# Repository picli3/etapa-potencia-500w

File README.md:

# etapa-potencia-500w

Barra de potencia de audio con múltiples transistores en paralelo, pensada para entregar alta corriente y robustez térmica en amplificadores de gran potencia.

## Qué incluye
- esquemáticos o archivos de diseño en KiCad
- PCB o documentación asociada
- base reutilizable para análisis, fabricación o mejora del proyecto

## Propósito general
Este repositorio busca concentrar el diseño de hardware del proyecto en un formato editable y reutilizable, facilitando pruebas, documentación y futuras iteraciones del circuito.

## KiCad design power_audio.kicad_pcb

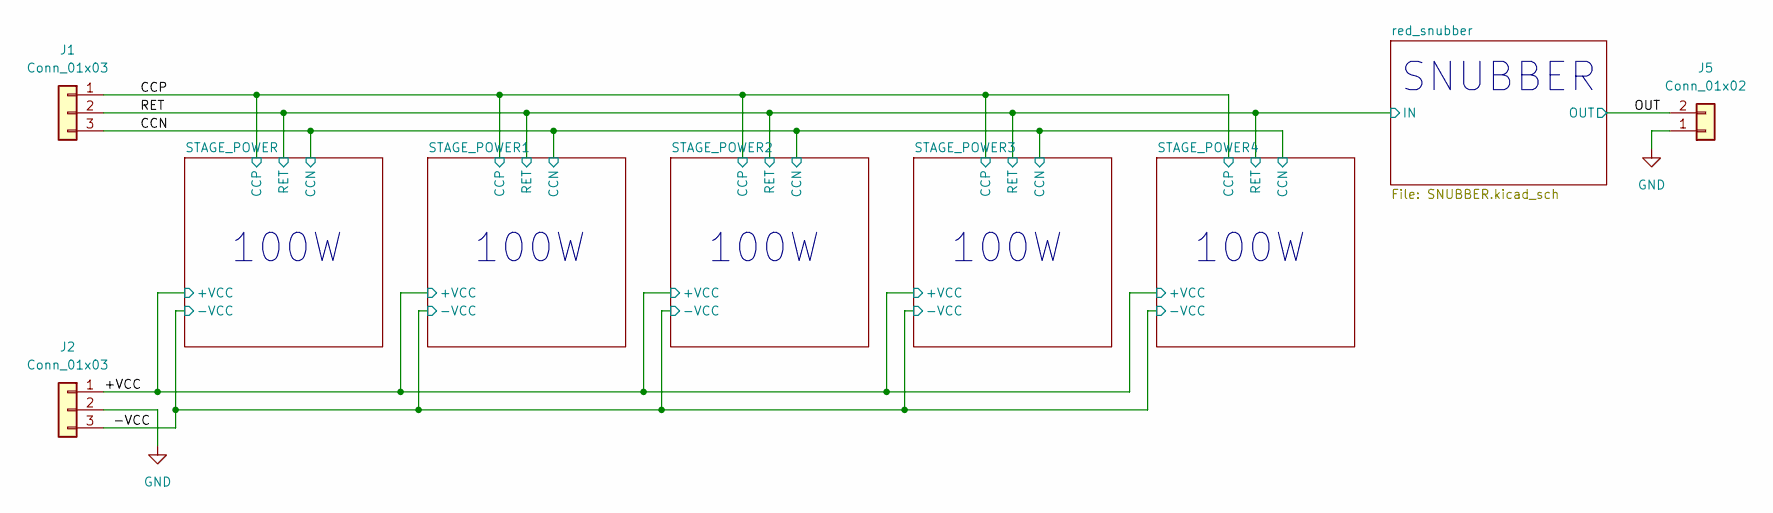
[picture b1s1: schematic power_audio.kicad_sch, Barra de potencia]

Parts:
J1, J2: Conn_01x03; TerminalBlock_Phoenix_MKDS-1,5-3-5.08_1x03_P5.08mm_Horizont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
J5: Conn_01x02; TerminalBlock_Phoenix_MKDS-1,5-2-5.08_1x02_P5.08mm_Horizont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

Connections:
/+VCC: J2.1; also elsewhere on the board
/-VCC: J2.3; also elsewhere on the board
/CCN: J1.3; also elsewhere on the board
/CCP: J1.1; also elsewhere on the board
/OUT: J5.2; also elsewhere on the board
/RET: J1.2; also elsewhere on the board
GND: J2.2, J5.1; also elsewhere on the board

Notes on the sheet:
100W
SNUBBER

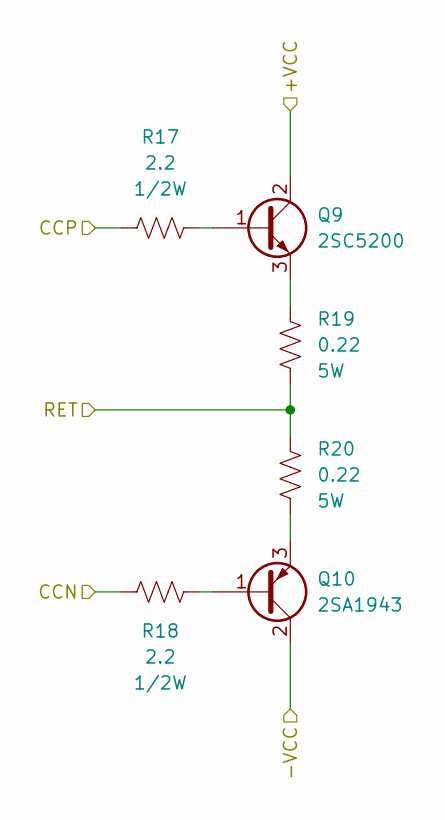
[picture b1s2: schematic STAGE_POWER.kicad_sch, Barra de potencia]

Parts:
Q9: 2SC5200; TO-264-3_Vertical; Mfr. Part 2SC5200OTU; LCSC Part C2920870
Q10: 2SA1943; TO-264-3_Vertical; Mfr. Part 2SA1943-O(Q); LCSC Part C480004
R17, R18: 2.2; R_Axial_DIN0309_L9.0mm_D3.2mm_P12.70mm_Horizontal
R19, R20: 0.22; R_Axial_Power_L25.0mm_W9.0mm_P27.94mm

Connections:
/+VCC: Q9.2 (C); also elsewhere on the board
/-VCC: Q10.2 (C); also elsewhere on the board
/CCN: R18.1; also elsewhere on the board
/CCP: R17.1; also elsewhere on the board
/RET: R19.1, R20.2; also elsewhere on the board
unnamed: Q9.1 (B), R17.2
unnamed: Q9.3 (E), R19.2
unnamed: Q10.1 (B), R18.2
unnamed: Q10.3 (E), R20.1

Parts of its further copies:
Q1, Q3, Q5, Q7: 2SC5200; TO-264-3_Vertical; Mfr. Part 2SC5200OTU; LCSC Part C2920870
Q2, Q4, Q6, Q8: 2SA1943; TO-264-3_Vertical; Mfr. Part 2SA1943-O(Q); LCSC Part C480004
R1, R2, R5, R6, R9, R10, R13, R14: 2.2; R_Axial_DIN0309_L9.0mm_D3.2mm_P12.70mm_Horizontal
R3, R7, R11, R15: 0.22; R_Axial_Power_L25.0mm_W9.0mm_P27.94mm

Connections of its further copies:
/+VCC: Q1.2 (C), Q3.2 (C), Q5.2 (C), Q7.2 (C); also elsewhere on the board
/-VCC: Q2.2 (C), Q4.2 (C), Q6.2 (C), Q8.2 (C); also elsewhere on the board
/CCN: R2.1, R6.1, R10.1, R14.1; also elsewhere on the board
/CCP: R1.1, R5.1, R9.1, R13.1; also elsewhere on the board
/RET: R3.1, R7.1, R11.1, R15.1; also elsewhere on the board
unnamed: Q1.1 (B), R1.2
unnamed: Q1.3 (E), R3.2
unnamed: Q2.1 (B), R2.2
unnamed 11: Q2.3 (E); also elsewhere on the board
unnamed: Q3.1 (B), R5.2
unnamed: Q3.3 (E), R7.2
unnamed: Q4.1 (B), R6.2
unnamed 15: Q4.3 (E); also elsewhere on the board
unnamed: Q5.1 (B), R9.2
unnamed: Q5.3 (E), R11.2
unnamed: Q6.1 (B), R10.2
unnamed 19: Q6.3 (E); also elsewhere on the board
unnamed: Q7.1 (B), R13.2
unnamed: Q7.3 (E), R15.2
unnamed: Q8.1 (B), R14.2
unnamed 23: Q8.3 (E); also elsewhere on the board

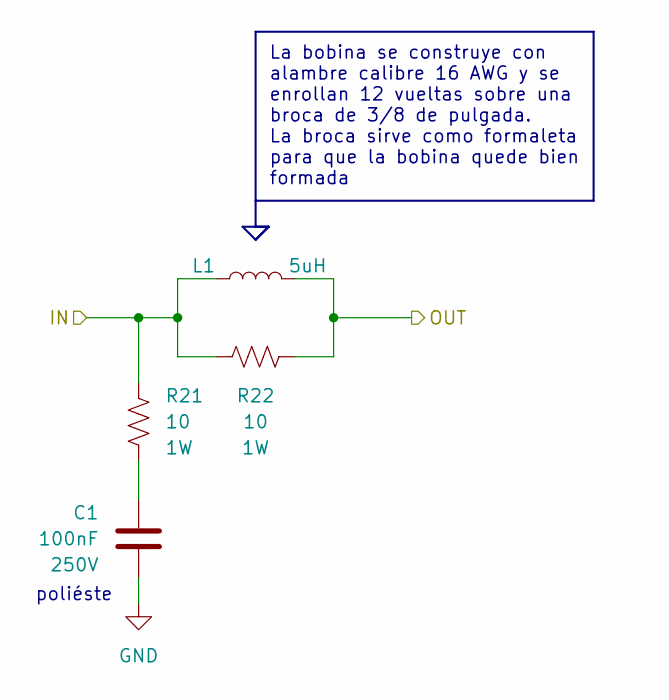
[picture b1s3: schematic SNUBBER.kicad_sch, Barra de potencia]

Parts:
C1: 100nF; C_Disc_D10.5mm_W5.0mm_P10.00mm; VOLTAGE 250V
L1: 5uH; L_Axial_L16.0mm_D9.5mm_P20.32mm_Horizontal_Vishay_IM-10-37
R21, R22: 10; R_Axial_DIN0414_L11.9mm_D4.5mm_P15.24mm_Horizontal

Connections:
/OUT: L1.2, R22.2; also elsewhere on the board
/RET: L1.1, R21.2, R22.1; also elsewhere on the board
GND: C1.2; also elsewhere on the board
unnamed: C1.1, R21.1

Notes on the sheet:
La bobina se construye con alambre calibre 16 AWG y se enrollan 12 vueltas sobre una broca de 3/8 de pulgada. La broca sirve como formaleta para que la bobina quede bien formada
poliéste

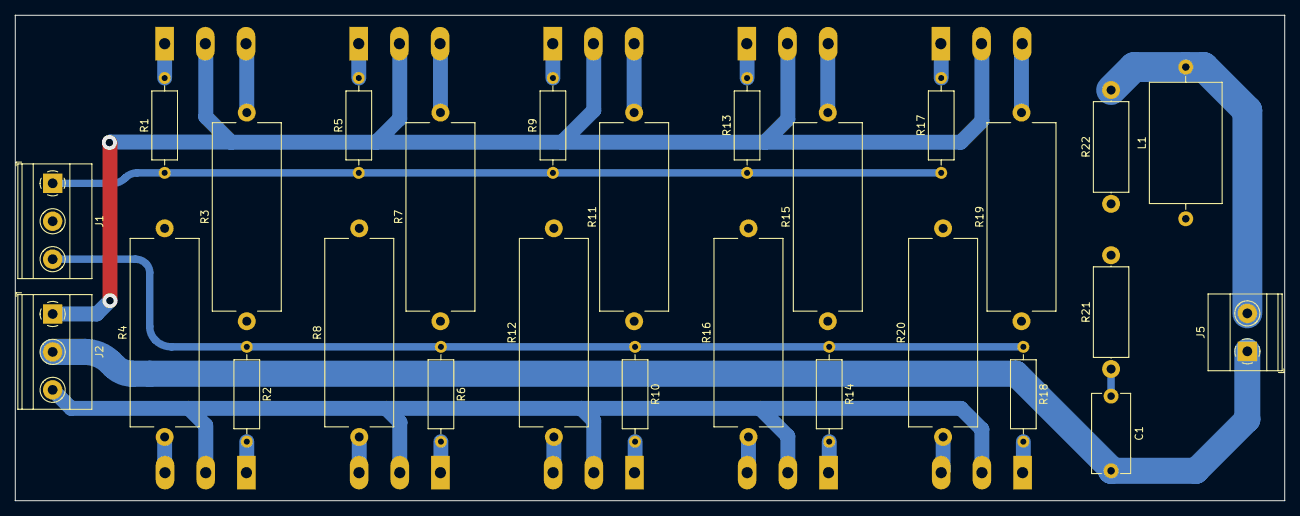
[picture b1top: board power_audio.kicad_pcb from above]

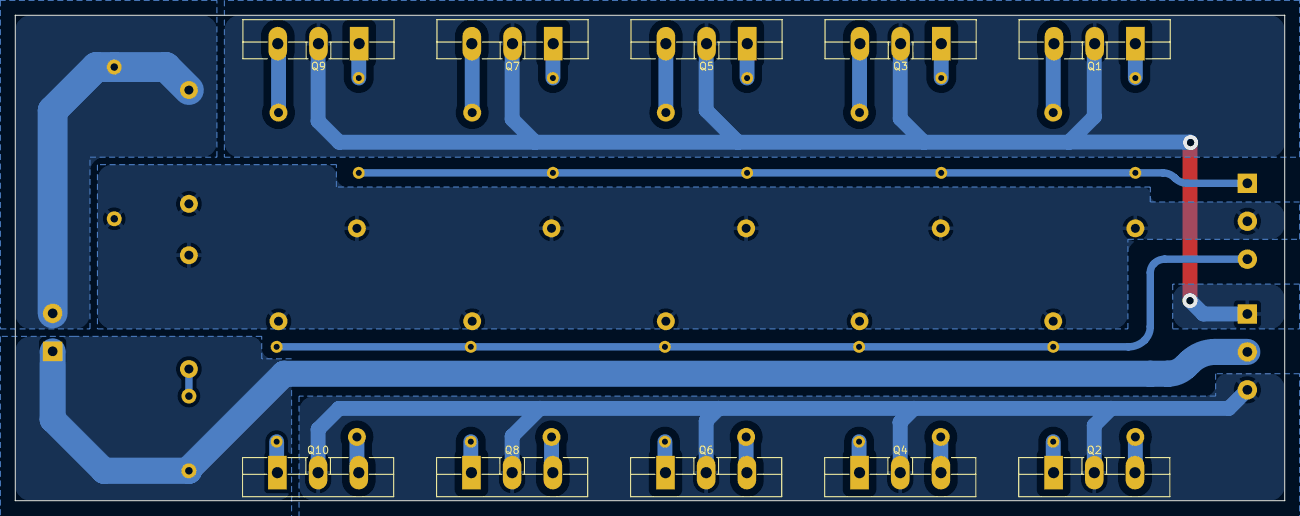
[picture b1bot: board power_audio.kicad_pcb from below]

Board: 2 copper layers, 170.0 x 65.0 mm, 37 parts (10 on the bottom side), 28 nets.

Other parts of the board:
R4, R8, R12, R16: 2.2; R_Axial_Power_L25.0mm_W9.0mm_P27.94mm

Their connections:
/RET: R4.2, R8.2, R12.2, R16.2; also elsewhere on the board
unnamed 11: R4.1; also elsewhere on the board
unnamed 15: R8.1; also elsewhere on the board
unnamed 19: R12.1; also elsewhere on the board
unnamed 23: R16.1; also elsewhere on the board

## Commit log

2023-03-11 agregando etapa de potencia
2023-03-11 agregando el circuito
2024-07-16 mejorando pistas
2026-04-29 Agrega README con descripción inicial del proyecto
